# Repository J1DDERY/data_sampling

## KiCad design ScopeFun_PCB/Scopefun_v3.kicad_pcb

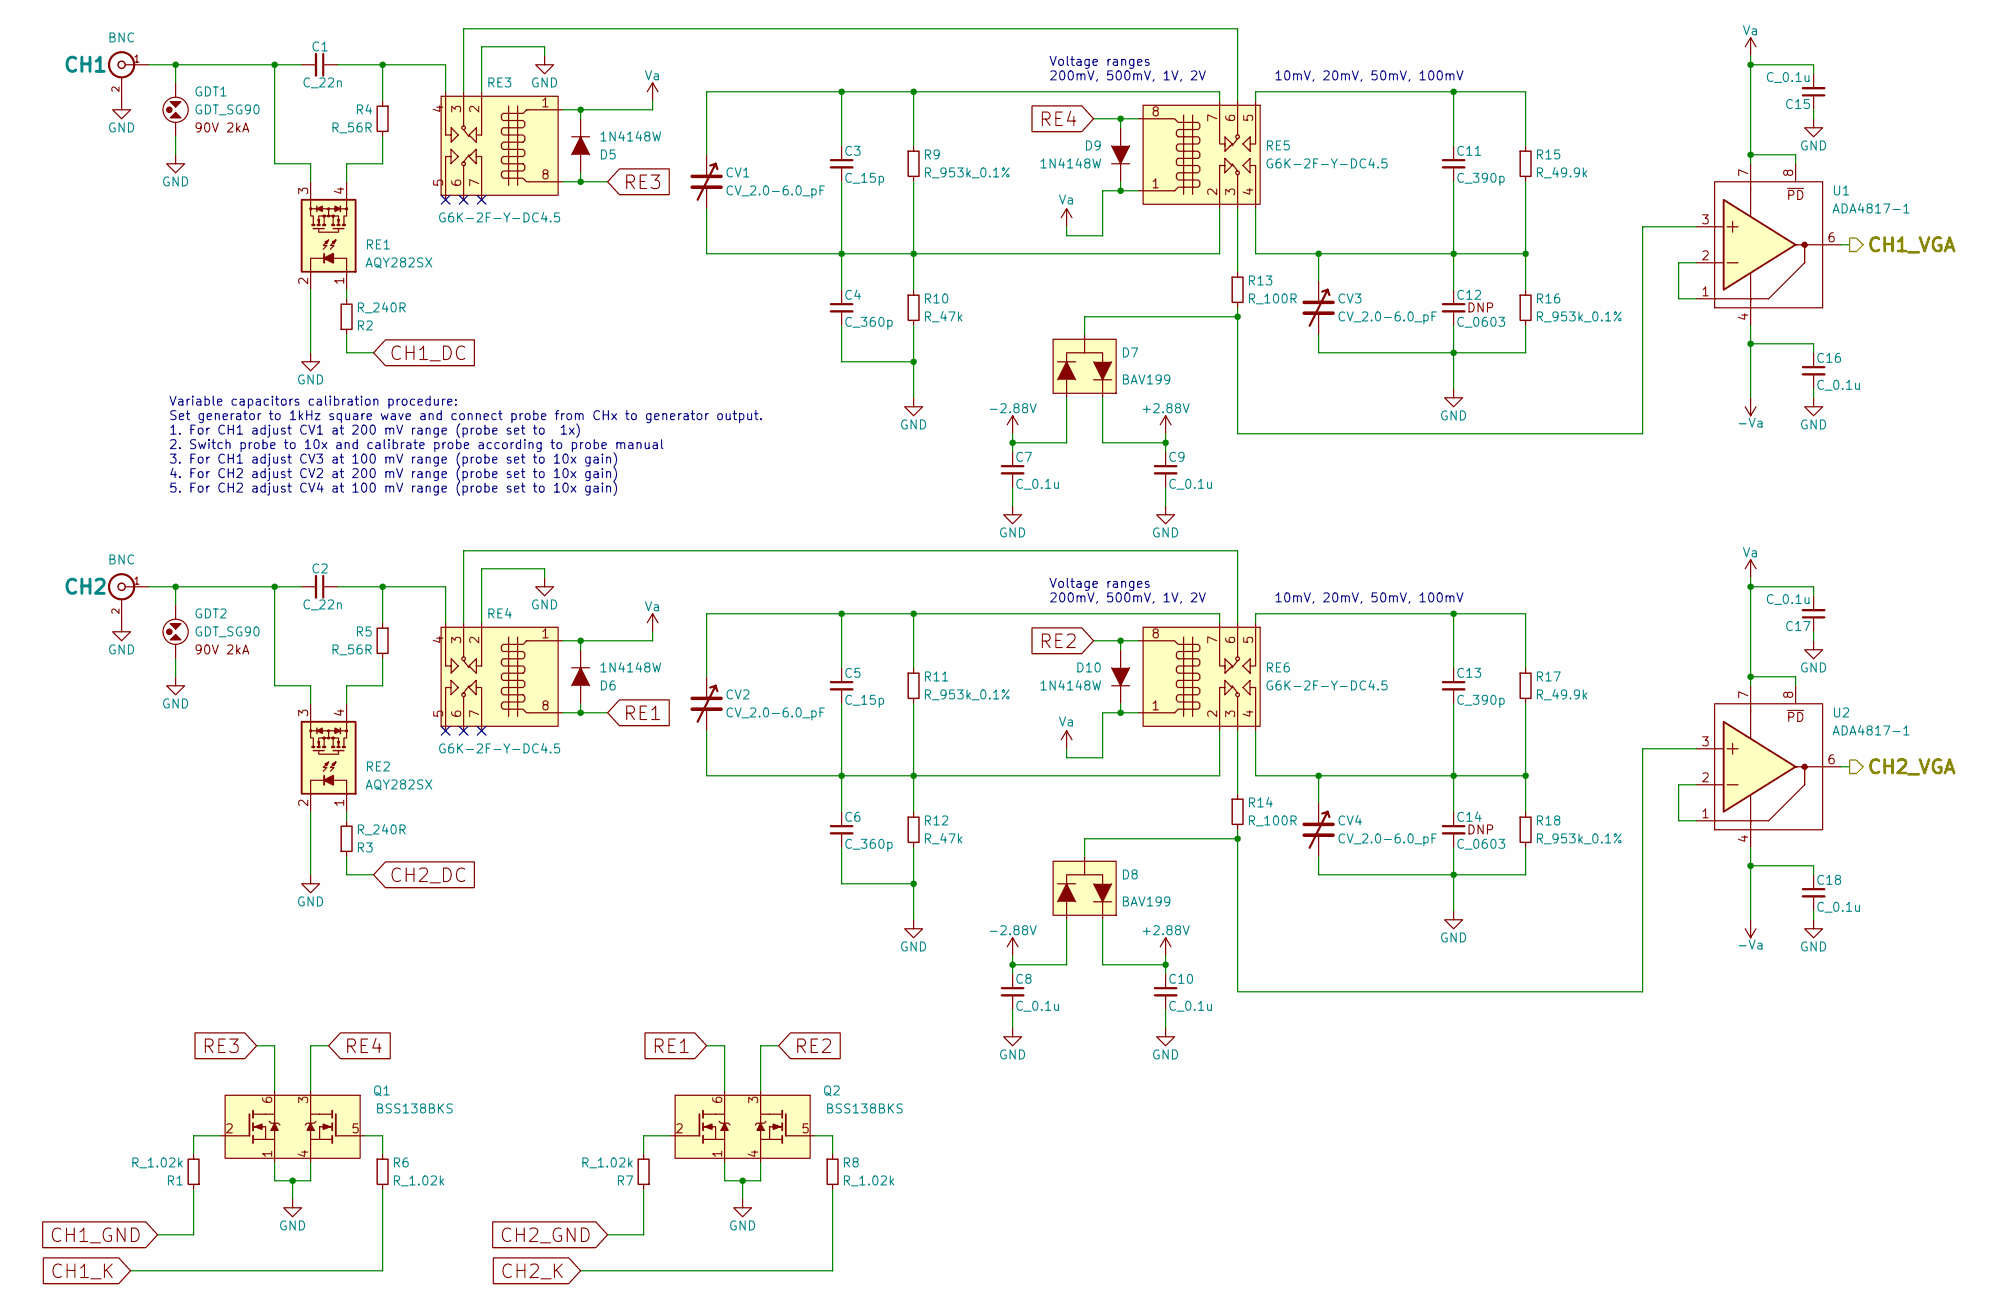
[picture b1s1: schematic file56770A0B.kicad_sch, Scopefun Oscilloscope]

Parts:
C1, C2: C_22n; C_0603; MFG Part# C0603C223K1RACTU
C3, C5: C_15p; C_0603; MFG Part# 885012006074
C4, C6: C_360p; C_0603; MFG Part# C0603C361G5GACTU
C7, C8, C9, C10, C15, C16, C17, C18: C_0.1u; C_0603; MFG Part# C0603C104K4RACTU
C11, C13: C_390p; C_0603; MFG Part# VJ0603A391GXAPW1BC
C12, C14: C_0603
CH1, CH2: BNC; BNC-5-1634556-0; MFG Part# 5-1634556-0
CV1, CV2, CV3, CV4: CV_2.0-6.0_pF; SGC3; MFG Part# SGC3S060
D5, D6, D9, D10: 1N4148W; SOD123; MFG Part# 1N4148W-7-F
D7, D8: BAV199; SOT23; MFG Part# BAV199-7-F
GDT1, GDT2: GDT_SG90; GDT_SG; MFG Part# SG90
Q1, Q2: BSS138BKS; SOT363; MFG Part# BSS138PS,115
R1, R6, R7, R8: R_1.02k; R_0603; MFG Part# ERJ-3EKF1021V
R2, R3: R_240R; R_0603; MFG Part# ERJ-3EKF2400V
R4, R5: R_56R; R_0603; MFG Part# ERJ-3EKF56R0V
R9, R11, R16, R18: R_953k_0.1%; R_0805; MFG Part# ERA-6AEB9533V
R10, R12: R_47k; R_0603; MFG Part# ERJ-3EKF4702V
R13, R14: R_100R; R_0603; MFG Part# ERJ-3EKF1000V
R15, R17: R_49.9k; R_0603; MFG Part# ERJ-3EKF4992V
RE1, RE2: AQY282SX; SOP-4; MFG Part# AQY282SX
RE3, RE4, RE5, RE6: G6K-2F-Y-DC4.5; G6K-2F-Y; MFG Part# G6K-2F-Y-DC4.5
U1, U2: ADA4817-1; SOIC8; MFG Part# ADA4817-1ARDZ

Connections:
+2.88V: C9.1, C10.1, D7.2, D8.2; also elsewhere on the board
-2.88V: C7.1, C8.1, D7.1, D8.1; also elsewhere on the board
-Va: C16.1, C18.1, U1.4 (-Vs), U2.4 (-Vs); also elsewhere on the board
/ANALOG INPUTS/CH1_VGA: U1.6 (OUT); also elsewhere on the board
/ANALOG INPUTS/CH2_VGA: U2.6 (OUT); also elsewhere on the board
CH1_DC: R2.1; also elsewhere on the board
CH1_GND: R1.1; also elsewhere on the board
CH1_K: R6.2; also elsewhere on the board
CH2_DC: R3.1; also elsewhere on the board
CH2_GND: R7.1; also elsewhere on the board
CH2_K: R8.2; also elsewhere on the board
GND: C4.2, C6.2, C7.2, C8.2, C9.2, C10.2, C12.2, C14.2, C15.1, C16.2, C17.1, C18.2, CH1.2 (Ext), CH2.2 (Ext), CV3.2, CV4.2, GDT1.2, GDT2.2, Q1.1 (S1), Q1.4 (S2), Q2.1 (S1), Q2.4 (S2), R10.2, R12.2, R16.2, R18.2, RE1.2, RE2.2, RE3.2, RE4.2; also elsewhere on the board
unnamed: C1.1, R4.1, RE3.4
unnamed: C2.1, R5.1, RE4.4
unnamed: C3.1, CV1.1, R9.1, RE5.7
unnamed: C3.2, C4.1, CV1.2, R9.2, R10.1, RE5.2
unnamed: C5.1, CV2.1, R11.1, RE6.7
unnamed: C5.2, C6.1, CV2.2, R11.2, R12.1, RE6.2
unnamed: C11.1, R15.1, RE5.5
unnamed: C11.2, C12.1, CV3.1, R15.2, R16.1, RE5.4
unnamed: C13.1, R17.1, RE6.5
unnamed: C13.2, C14.1, CV4.1, R17.2, R18.1, RE6.4
unnamed: C1.2, CH1.1 (In), GDT1.1, RE1.3
unnamed: C2.2, CH2.1 (In), GDT2.1, RE2.3
unnamed: Q1.2 (G1), R1.2
unnamed: Q1.5 (G2), R6.1
unnamed: Q2.2 (G1), R7.2
unnamed: Q2.5 (G2), R8.1
unnamed: R2.2, RE1.1
unnamed: R3.2, RE2.1
unnamed: R4.2, RE1.4
unnamed: R5.2, RE2.4
unnamed: R13.1, RE5.3
unnamed: R14.1, RE6.3
unnamed: RE3.3, RE5.6
unnamed: RE4.3, RE6.6
unnamed: D7.3, R13.2, U1.3 (+IN)
unnamed: U1.1 (FB), U1.2 (-IN)
unnamed: D8.3, R14.2, U2.3 (+IN)
unnamed: U2.1 (FB), U2.2 (-IN)
RE1: D6.2 (A), Q2.6 (D1), RE4.8
RE2: D10.2 (A), Q2.3 (D2), RE6.8
RE3: D5.2 (A), Q1.6 (D1), RE3.8
RE4: D9.2 (A), Q1.3 (D2), RE5.8
Va: C15.2, C17.2, D5.1 (K), D6.1 (K), D9.1 (K), D10.1 (K), RE3.1, RE4.1, RE5.1, RE6.1, U1.7 (+Vs), U1.8 (~PD), U2.7 (+Vs), U2.8 (~PD); also elsewhere on the board

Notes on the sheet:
10mV, 20mV, 50mV, 100mV
Voltage ranges 200mV, 500mV, 1V, 2V
Variable capacitors calibration procedure: Set generator to 1kHz square wave and connect probe from CHx to generator output. 1. For CH1 adjust CV1 at 200 mV range (probe set to 1x) 2. Switch probe to 10x and calibrate probe according to probe manual 3. For CH1 adjust CV3 at 100 mV range (probe set 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

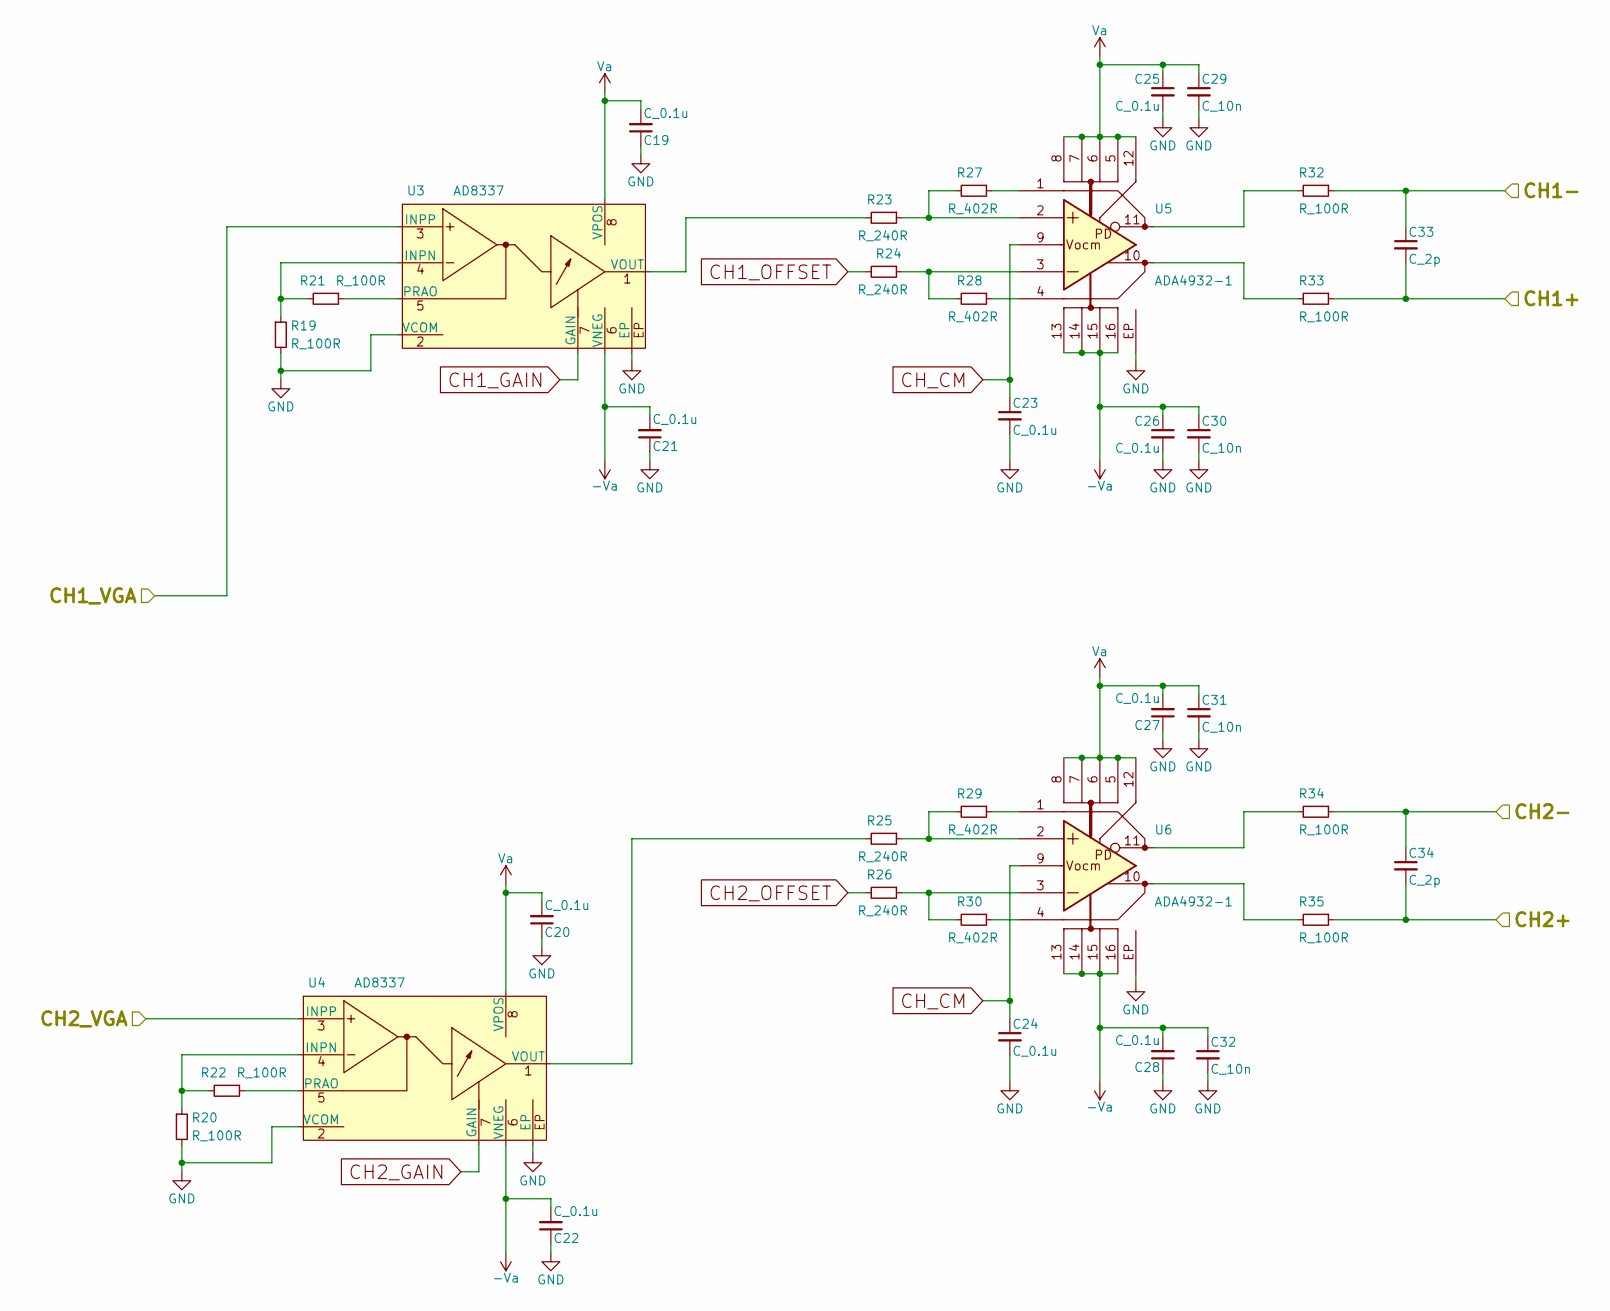
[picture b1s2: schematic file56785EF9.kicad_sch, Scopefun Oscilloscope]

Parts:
C19, C20, C21, C22, C23, C24, C25, C26, C27, C28: C_0.1u; C_0603; MFG Part# C0603C104K4RACTU
C29, C30, C31, C32: C_10n; C_0402; MFG Part# 885012205012
C33, C34: C_2p; C_0603; MFG Part# C1608C0G2A020C080AA
R19, R20, R21, R22, R32, R33, R34, R35: R_100R; R_0603; MFG Part# ERJ-3EKF1000V
R23, R24, R25, R26: R_240R; R_0603; MFG Part# ERJ-3EKF2400V
R27, R28, R29, R30: R_402R; R_0603; MFG Part# ERJ-3EKF4020V
U3, U4: AD8337; CP-8-2; MFG Part# AD8337BCPZ-REEL7
U5, U6: ADA4932-1; CP-16-2; MFG Part# ADA4932-1YCPZ-R7

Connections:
-Va: C21.2, C22.2, C26.1, C28.2, C30.1, C32.1, U3.6 (VNEG), U4.6 (VNEG), U5.13 (-Vs), U5.14 (-Vs), U5.15 (-Vs), U5.16 (-Vs), U6.13 (-Vs), U6.14 (-Vs), U6.15 (-Vs), U6.16 (-Vs); also elsewhere on the board
/ADC/CH1+: C33.2, R33.1; also elsewhere on the board
/ADC/CH1-: C33.1, R32.1; also elsewhere on the board
/ADC/CH2+: C34.2, R35.1; also elsewhere on the board
/ADC/CH2-: C34.1, R34.1; also elsewhere on the board
/ANALOG INPUTS/CH1_VGA: U3.3 (INPP); also elsewhere on the board
/ANALOG INPUTS/CH2_VGA: U4.3 (INPP); also elsewhere on the board
CH1_GAIN: U3.7 (GAIN); also elsewhere on the board
CH1_OFFSET: R24.2; also elsewhere on the board
CH2_GAIN: U4.7 (GAIN); also elsewhere on the board
CH2_OFFSET: R26.2; also elsewhere on the board
CH_CM: C23.1, C24.1, U5.9 (Vocm), U6.9 (Vocm); also elsewhere on the board
GND: C19.1, C20.1, C21.1, C22.1, C23.2, C24.2, C25.2, C26.2, C27.1, C28.1, C29.2, C30.2, C31.2, C32.2, R19.2, R20.2, U3.2 (VCOM), U3.EP, U4.2 (VCOM), U4.EP, U5.EP, U6.EP; also elsewhere on the board
unnamed: R19.1, R21.2, U3.4 (INPN)
unnamed: R21.1, U3.5 (PRAO)
unnamed: R23.2, U3.1 (VOUT)
unnamed: R20.1, R22.2, U4.4 (INPN)
unnamed: R22.1, U4.5 (PRAO)
unnamed: R25.2, U4.1 (VOUT)
unnamed: R28.1, U5.4 (+FB)
unnamed: R23.1, R27.2, U5.2 (+IN)
unnamed: R33.2, U5.10 (+OUT)
unnamed: R27.1, U5.1 (-FB)
unnamed: R24.1, R28.2, U5.3 (-IN)
unnamed: R32.2, U5.11 (-OUT)
unnamed: R30.1, U6.4 (+FB)
unnamed: R25.1, R29.2, U6.2 (+IN)
unnamed: R35.2, U6.10 (+OUT)
unnamed: R29.1, U6.1 (-FB)
unnamed: R26.1, R30.2, U6.3 (-IN)
unnamed: R34.2, U6.11 (-OUT)
Va: C19.2, C20.2, C25.1, C27.2, C29.1, C31.1, U3.8 (VPOS), U4.8 (VPOS), U5.5 (+Vs), U5.6 (+Vs), U5.7 (+Vs), U5.8 (+Vs), U5.12 (r~PD), U6.5 (+Vs), U6.6 (+Vs), U6.7 (+Vs), U6.8 (+Vs), U6.12 (r~PD); also elsewhere on the board

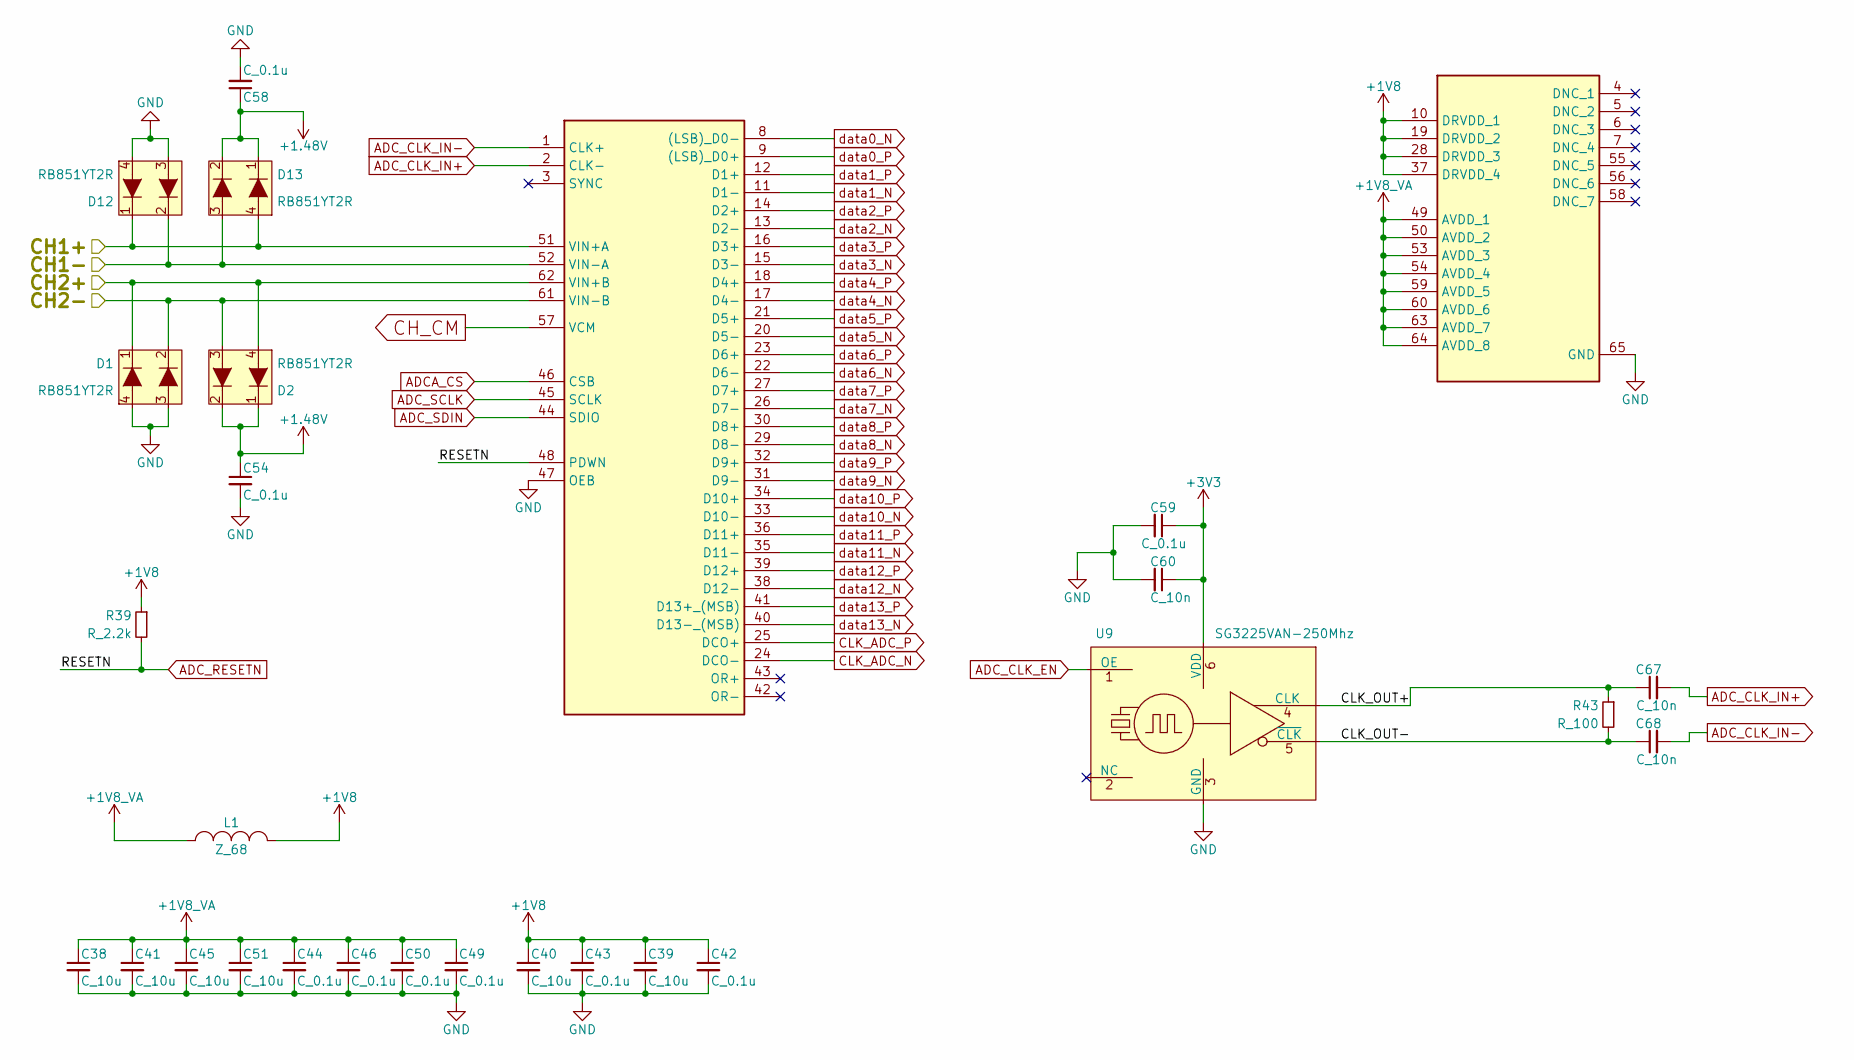
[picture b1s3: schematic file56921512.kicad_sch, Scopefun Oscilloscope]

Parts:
C38, C39, C40, C41, C45, C51: C_10u; C_0603; MFG Part# C0603C104K4RACTU
C42, C43, C44, C46, C49, C50, C54, C58, C59: C_0.1u; C_0603; MFG Part# C0603C104K4RACTU
C60, C67, C68: C_10n; C_0402; MFG Part# 885012205012
D1, D2, D12, D13: RB851YT2R; SOT-543; MFG Part# RB851YT2R
IC1: AD9643BCPZ-250; QFN50P900X900X100-65N-D; Manufacturer_Part_Number AD9643BCPZ-250; Mouser Part Number 584-AD9643BCPZ-250
L1: Z_68; L_0805; MFG Part# 782853680
R39: R_2.2k; R_0603; MFG Part# ERJ-3EKF2201V
R43: R_100; R_0402; MFG Part# ERJ-2RKF1000X
U9: SG3225VAN-250Mhz; 3.2X2.5_SMD_6_EPSON; MFG Part# SG3225VAN 250.000000M-KEGA3

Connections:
+1.48V: C54.1, C58.1, D2.1, D2.2, D13.1, D13.2; also elsewhere on the board
+1V8: C39.1, C40.1, C42.1, C43.1, IC1.10 (DRVDD_1), IC1.19 (DRVDD_2), IC1.28 (DRVDD_3), IC1.37 (DRVDD_4), L1.1, R39.1; also elsewhere on the board
+1V8_VA: C38.1, C41.1, C44.1, C45.1, C46.1, C49.1, C50.1, C51.1, IC1.49 (AVDD_1), IC1.50 (AVDD_2), IC1.53 (AVDD_3), IC1.54 (AVDD_4), IC1.59 (AVDD_5), IC1.60 (AVDD_6), IC1.63 (AVDD_7), IC1.64 (AVDD_8), L1.2
+3V3: C59.1, C60.1, U9.6 (VDD); also elsewhere on the board
/ADC/CH1+: D12.1, D13.4, IC1.51 (VIN+A); also elsewhere on the board
/ADC/CH1-: D12.2, D13.3, IC1.52 (VIN-A); also elsewhere on the board
/ADC/CH2+: D1.1, D2.4, IC1.62 (VIN+B); also elsewhere on the board
/ADC/CH2-: D1.2, D2.3, IC1.61 (VIN-B); also elsewhere on the board
/ADC/CLK_OUT+: C67.1, R43.1, U9.4 (CLK)
/ADC/CLK_OUT-: C68.1, R43.2, U9.5 (~CLK)
ADCA_CS: IC1.46 (CSB); also elsewhere on the board
ADC_CLK_EN: U9.1 (OE); also elsewhere on the board
ADC_CLK_IN+: C67.2, IC1.2 (CLK-)
ADC_CLK_IN-: C68.2, IC1.1 (CLK+)
ADC_RESETN: IC1.48 (PDWN), R39.2; also elsewhere on the board
ADC_SCLK: IC1.45 (SCLK); also elsewhere on the board
ADC_SDIN: IC1.44 (SDIO); also elsewhere on the board
CH_CM: IC1.57 (VCM); also elsewhere on the board
CLK_ADC_N: IC1.24 (DCO-); also elsewhere on the board
CLK_ADC_P: IC1.25 (DCO+); also elsewhere on the board
GND: C38.2, C39.2, C40.2, C41.2, C42.2, C43.2, C44.2, C45.2, C46.2, C49.2, C50.2, C51.2, C54.2, C58.2, C59.2, C60.2, D1.3, D1.4, D12.3, D12.4, IC1.47 (OEB), IC1.65 (GND), U9.3 (GND); also elsewhere on the board
data0_N: IC1.8 ((LSB)_D0-); also elsewhere on the board
data0_P: IC1.9 ((LSB)_D0+); also elsewhere on the board
data1_N: IC1.11 (D1-); also elsewhere on the board
data1_P: IC1.12 (D1+); also elsewhere on the board
data2_N: IC1.13 (D2-); also elsewhere on the board
data2_P: IC1.14 (D2+); also elsewhere on the board
data3_N: IC1.15 (D3-); also elsewhere on the board
data3_P: IC1.16 (D3+); also elsewhere on the board
data4_N: IC1.17 (D4-); also elsewhere on the board
data4_P: IC1.18 (D4+); also elsewhere on the board
data5_N: IC1.20 (D5-); also elsewhere on the board
data5_P: IC1.21 (D5+); also elsewhere on the board
data6_N: IC1.22 (D6-); also elsewhere on the board
data6_P: IC1.23 (D6+); also elsewhere on the board
data7_N: IC1.26 (D7-); also elsewhere on the board
data7_P: IC1.27 (D7+); also elsewhere on the board
data8_N: IC1.29 (D8-); also elsewhere on the board
data8_P: IC1.30 (D8+); also elsewhere on the board
data9_N: IC1.31 (D9-); also elsewhere on the board
data9_P: IC1.32 (D9+); also elsewhere on the board
data10_N: IC1.33 (D10-); also elsewhere on the board
data10_P: IC1.34 (D10+); also elsewhere on the board
data11_N: IC1.35 (D11-); also elsewhere on the board
data11_P: IC1.36 (D11+); also elsewhere on the board
data12_N: IC1.38 (D12-); also elsewhere on the board
data12_P: IC1.39 (D12+); also elsewhere on the board
data13_N: IC1.40 (D13-_(MSB)); also elsewhere on the board
data13_P: IC1.41 (D13+_(MSB)); also elsewhere on the board

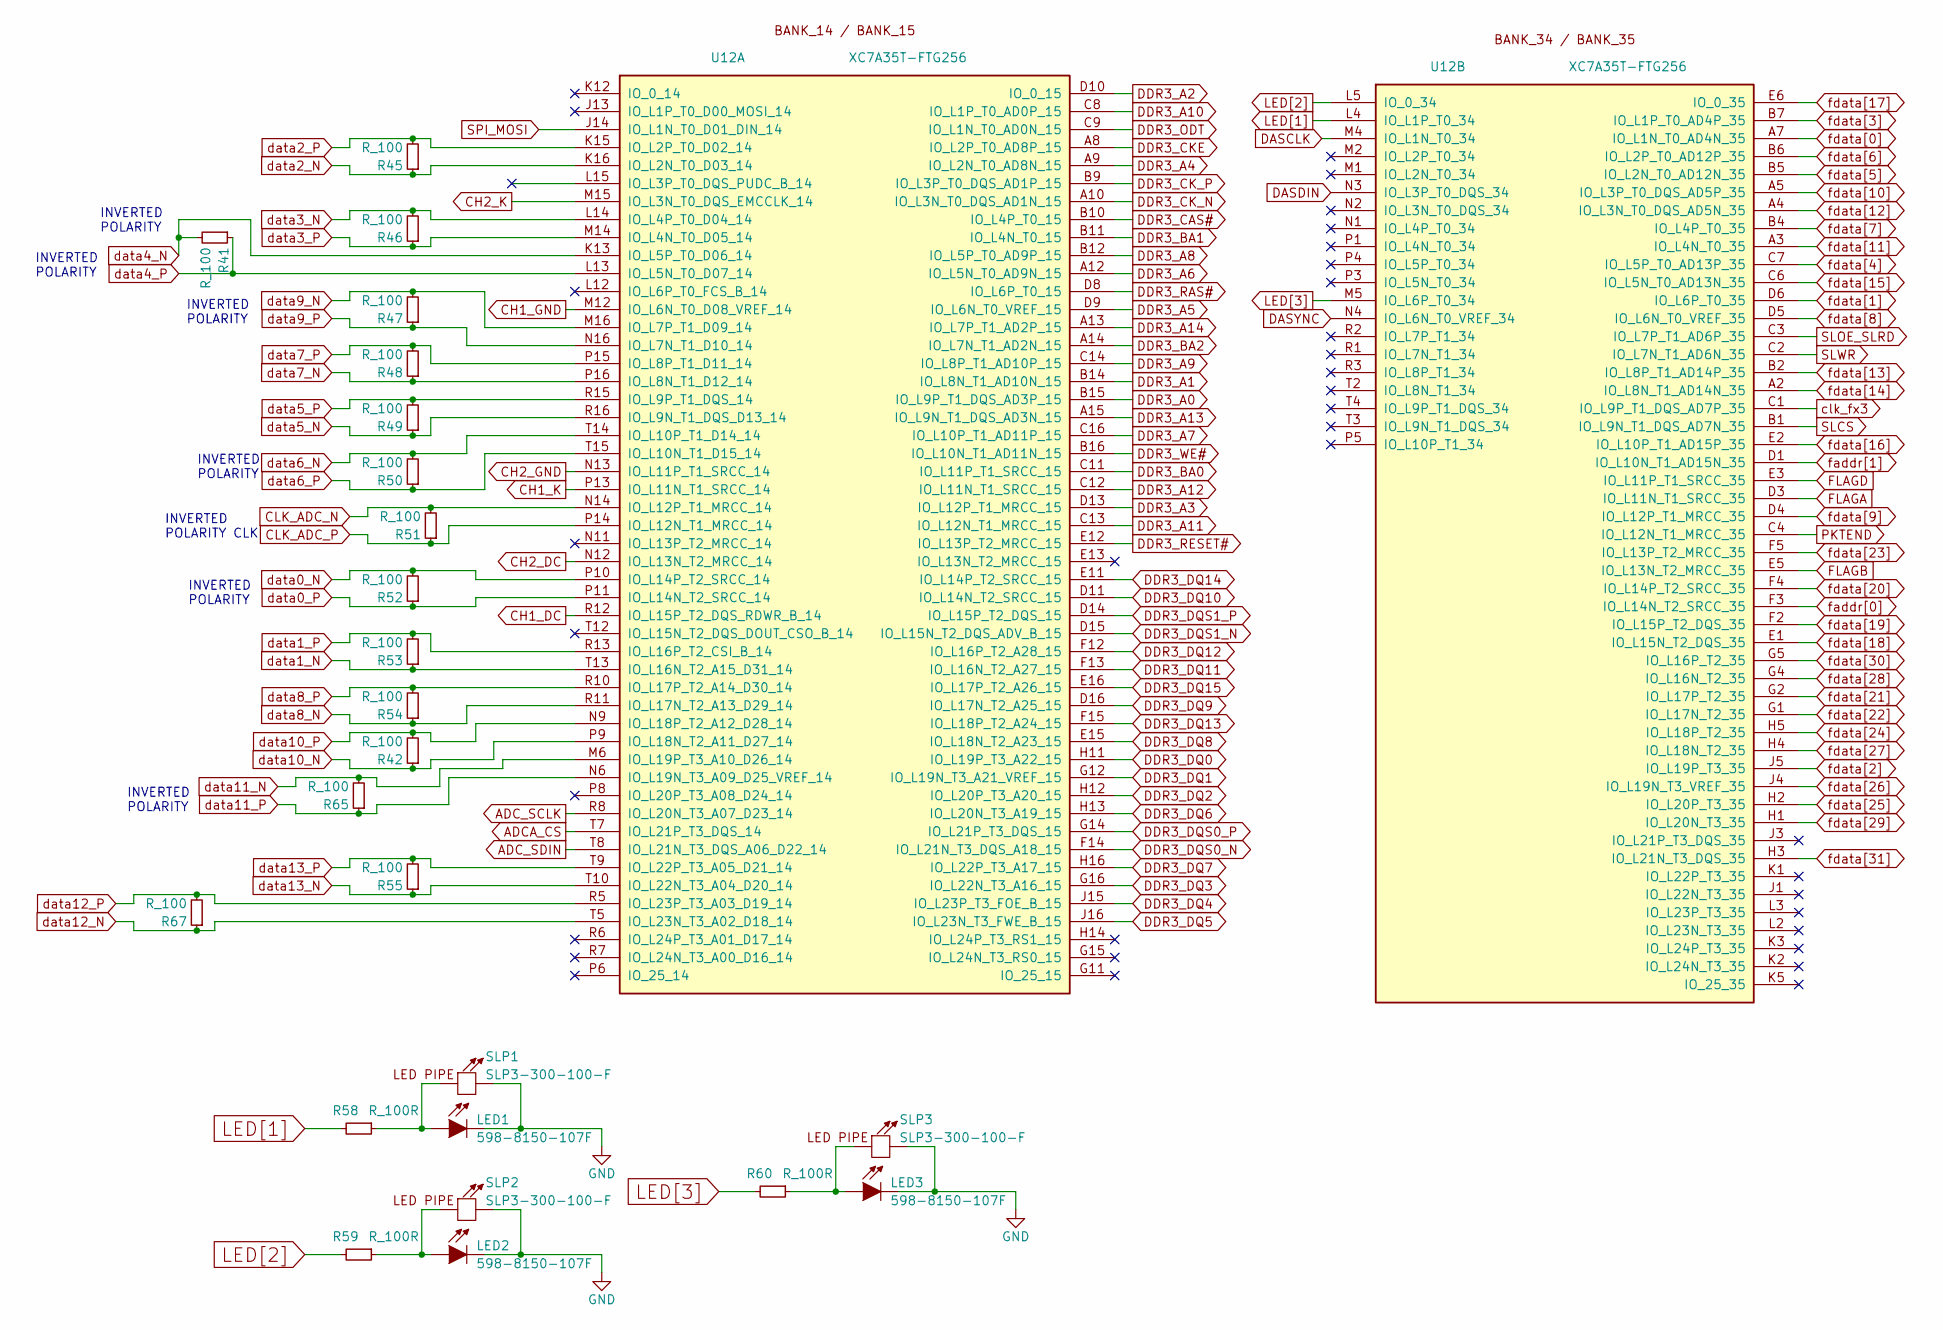
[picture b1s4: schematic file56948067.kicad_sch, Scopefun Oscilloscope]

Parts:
LED1, LED2, LED3: 598-8150-107F; LED_0805; MFG Part# 598-8150-107F
R41, R42, R45, R46, R47, R48, R49, R50, R51, R52, R53, R54, R55, R65, R67: R_100; R_0402; MFG Part# ERJ-2RKF1000X
R58, R59, R60: R_100R; R_0603; MFG Part# ERJ-3EKF1000V
SLP1, SLP2, SLP3: SLP3-300-100-F; SLP3-300-100-R; MFG Part# SLP3-300-100-F
U12: XC7A35T-FTG256; BGA256_FTG256; MFG Part# XC7A35T-2FTG256I

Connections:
ADCA_CS: U12.T7 (IO_L21P_T3_DQS_14); also elsewhere on the board
ADC_SCLK: U12.R8 (IO_L20N_T3_A07_D23_14); also elsewhere on the board
ADC_SDIN: U12.T8 (IO_L21N_T3_DQS_A06_D22_14); also elsewhere on the board
CH1_DC: U12.R12 (IO_L15P_T2_DQS_RDWR_B_14); also elsewhere on the board
CH1_GND: U12.M12 (IO_L6N_T0_D08_VREF_14); also elsewhere on the board
CH1_K: U12.P13 (IO_L11N_T1_SRCC_14); also elsewhere on the board
CH2_DC: U12.N12 (IO_L13N_T2_MRCC_14); also elsewhere on the board
CH2_GND: U12.N13 (IO_L11P_T1_SRCC_14); also elsewhere on the board
CH2_K: U12.M15 (IO_L3N_T0_DQS_EMCCLK_14); also elsewhere on the board
CLK_ADC_N: R51.2, U12.N14 (IO_L12P_T1_MRCC_14); also elsewhere on the board
CLK_ADC_P: R51.1, U12.P14 (IO_L12N_T1_MRCC_14); also elsewhere on the board
DASCLK: U12.M4 (IO_L1N_T0_34); also elsewhere on the board
DASDIN: U12.N3 (IO_L3P_T0_DQS_34); also elsewhere on the board
DASYNC: U12.N4 (IO_L6N_T0_VREF_34); also elsewhere on the board
DDR3_A0: U12.B15 (IO_L9P_T1_DQS_AD3P_15); also elsewhere on the board
DDR3_A1: U12.B14 (IO_L8N_T1_AD10N_15); also elsewhere on the board
DDR3_A2: U12.D10 (IO_0_15); also elsewhere on the board
DDR3_A3: U12.D13 (IO_L12P_T1_MRCC_15); also elsewhere on the board
DDR3_A4: U12.A9 (IO_L2N_T0_AD8N_15); also elsewhere on the board
DDR3_A5: U12.D9 (IO_L6N_T0_VREF_15); also elsewhere on the board
DDR3_A6: U12.A12 (IO_L5N_T0_AD9N_15); also elsewhere on the board
DDR3_A7: U12.C16 (IO_L10P_T1_AD11P_15); also elsewhere on the board
DDR3_A8: U12.B12 (IO_L5P_T0_AD9P_15); also elsewhere on the board
DDR3_A9: U12.C14 (IO_L8P_T1_AD10P_15); also elsewhere on the board
DDR3_A10: U12.C8 (IO_L1P_T0_AD0P_15); also elsewhere on the board
DDR3_A11: U12.C13 (IO_L12N_T1_MRCC_15); also elsewhere on the board
DDR3_A12: U12.C12 (IO_L11N_T1_SRCC_15); also elsewhere on the board
DDR3_A13: U12.A15 (IO_L9N_T1_DQS_AD3N_15); also elsewhere on the board
DDR3_A14: U12.A13 (IO_L7P_T1_AD2P_15); also elsewhere on the board
DDR3_BA0: U12.C11 (IO_L11P_T1_SRCC_15); also elsewhere on the board
DDR3_BA1: U12.B11 (IO_L4N_T0_15); also elsewhere on the board
DDR3_BA2: U12.A14 (IO_L7N_T1_AD2N_15); also elsewhere on the board
DDR3_CAS#: U12.B10 (IO_L4P_T0_15); also elsewhere on the board
DDR3_CKE: U12.A8 (IO_L2P_T0_AD8P_15); also elsewhere on the board
DDR3_CK_N: U12.A10 (IO_L3N_T0_DQS_AD1N_15); also elsewhere on the board
DDR3_CK_P: U12.B9 (IO_L3P_T0_DQS_AD1P_15); also elsewhere on the board
DDR3_DQ0: U12.H11 (IO_L19P_T3_A22_15); also elsewhere on the board
DDR3_DQ1: U12.G12 (IO_L19N_T3_A21_VREF_15); also elsewhere on the board
DDR3_DQ2: U12.H12 (IO_L20P_T3_A20_15); also elsewhere on the board
DDR3_DQ3: U12.G16 (IO_L22N_T3_A16_15); also elsewhere on the board
DDR3_DQ4: U12.J15 (IO_L23P_T3_FOE_B_15); also elsewhere on the board
DDR3_DQ5: U12.J16 (IO_L23N_T3_FWE_B_15); also elsewhere on the board
DDR3_DQ6: U12.H13 (IO_L20N_T3_A19_15); also elsewhere on the board
DDR3_DQ7: U12.H16 (IO_L22P_T3_A17_15); also elsewhere on the board
DDR3_DQ8: U12.E15 (IO_L18N_T2_A23_15); also elsewhere on the board
DDR3_DQ9: U12.D16 (IO_L17N_T2_A25_15); also elsewhere on the board
DDR3_DQ10: U12.D11 (IO_L14N_T2_SRCC_15); also elsewhere on the board
DDR3_DQ11: U12.F13 (IO_L16N_T2_A27_15); also elsewhere on the board
DDR3_DQ12: U12.F12 (IO_L16P_T2_A28_15); also elsewhere on the board
DDR3_DQ13: U12.F15 (IO_L18P_T2_A24_15); also elsewhere on the board
DDR3_DQ14: U12.E11 (IO_L14P_T2_SRCC_15); also elsewhere on the board
DDR3_DQ15: U12.E16 (IO_L17P_T2_A26_15); also elsewhere on the board
DDR3_DQS0_N: U12.F14 (IO_L21N_T3_DQS_A18_15); also elsewhere on the board
DDR3_DQS0_P: U12.G14 (IO_L21P_T3_DQS_15); also elsewhere on the board
DDR3_DQS1_N: U12.D15 (IO_L15N_T2_DQS_ADV_B_15); also elsewhere on the board
DDR3_DQS1_P: U12.D14 (IO_L15P_T2_DQS_15); also elsewhere on the board
DDR3_ODT: U12.C9 (IO_L1N_T0_AD0N_15); also elsewhere on the board
DDR3_RAS#: U12.D8 (IO_L6P_T0_15); also elsewhere on the board
DDR3_RESET#: U12.E12 (IO_L13P_T2_MRCC_15); also elsewhere on the board
DDR3_WE#: U12.B16 (IO_L10N_T1_AD11N_15); also elsewhere on the board
FLAGA: U12.D3 (IO_L11N_T1_SRCC_35); also elsewhere on the board
FLAGB: U12.E5 (IO_L13N_T2_MRCC_35); also elsewhere on the board
FLAGD: U12.E3 (IO_L11P_T1_SRCC_35); also elsewhere on the board
GND: LED1.1 (K), LED2.1 (K), LED3.1 (K), SLP1.1 (K), SLP2.1 (K), SLP3.1 (K); also elsewhere on the board
LED[1]: R58.2, U12.L4 (IO_L1P_T0_34)
LED[2]: R59.2, U12.L5 (IO_0_34)
LED[3]: R60.2, U12.M5 (IO_L6P_T0_34)
unnamed: LED1.2 (A), R58.1, SLP1.2 (A)
unnamed: LED2.2 (A), R59.1, SLP2.2 (A)
unnamed: LED3.2 (A), R60.1, SLP3.2 (A)
PKTEND: U12.C4 (IO_L12N_T1_MRCC_35); also elsewhere on the board
RE7: U12.L12 (IO_L6P_T0_FCS_B_14)
SLCS: U12.B1 (IO_L9N_T1_DQS_AD7N_35); also elsewhere on the board
SLOE_SLRD: U12.C3 (IO_L7P_T1_AD6P_35); also elsewhere on the board
SLWR: U12.C2 (IO_L7N_T1_AD6N_35); also elsewhere on the board
SPI_MOSI: U12.J14 (IO_L1N_T0_D01_DIN_14); also elsewhere on the board
clk_fx3: U12.C1 (IO_L9P_T1_DQS_AD7P_35); also elsewhere on the board
data0_N: R52.2, U12.P10 (IO_L14P_T2_SRCC_14); also elsewhere on the board
data0_P: R52.1, U12.P11 (IO_L14N_T2_SRCC_14); also elsewhere on the board
data1_N: R53.1, U12.T13 (IO_L16N_T2_A15_D31_14); also elsewhere on the board
data1_P: R53.2, U12.R13 (IO_L16P_T2_CSI_B_14); also elsewhere on the board
data2_N: R45.1, U12.K16 (IO_L2N_T0_D03_14); also elsewhere on the board
data2_P: R45.2, U12.K15 (IO_L2P_T0_D02_14); also elsewhere on the board
data3_N: R46.2, U12.L14 (IO_L4P_T0_D04_14); also elsewhere on the board
data3_P: R46.1, U12.M14 (IO_L4N_T0_D05_14); also elsewhere on the board
data4_N: R41.2, U12.K13 (IO_L5P_T0_D06_14); also elsewhere on the board
data4_P: R41.1, U12.L13 (IO_L5N_T0_D07_14); also elsewhere on the board
data5_N: R49.1, U12.R16 (IO_L9N_T1_DQS_D13_14); also elsewhere on the board
data5_P: R49.2, U12.R15 (IO_L9P_T1_DQS_14); also elsewhere on the board
data6_N: R50.2, U12.T14 (IO_L10P_T1_D14_14); also elsewhere on the board
data6_P: R50.1, U12.T15 (IO_L10N_T1_D15_14); also elsewhere on the board
data7_N: R48.1, U12.P16 (IO_L8N_T1_D12_14); also elsewhere on the board
data7_P: R48.2, U12.P15 (IO_L8P_T1_D11_14); also elsewhere on the board
data8_N: R54.1, U12.R11 (IO_L17N_T2_A13_D29_14); also elsewhere on the board
data8_P: R54.2, U12.R10 (IO_L17P_T2_A14_D30_14); also elsewhere on the board
data9_N: R47.2, U12.M16 (IO_L7P_T1_D09_14); also elsewhere on the board
data9_P: R47.1, U12.N16 (IO_L7N_T1_D10_14); also elsewhere on the board
data10_N: R42.1, U12.P9 (IO_L18N_T2_A11_D27_14); also elsewhere on the board
data10_P: R42.2, U12.N9 (IO_L18P_T2_A12_D28_14); also elsewhere on the board
data11_N: R65.2, U12.M6 (IO_L19P_T3_A10_D26_14); also elsewhere on the board
data11_P: R65.1, U12.N6 (IO_L19N_T3_A09_D25_VREF_14); also elsewhere on the board
data12_N: R67.1, U12.T5 (IO_L23N_T3_A02_D18_14); also elsewhere on the board
data12_P: R67.2, U12.R5 (IO_L23P_T3_A03_D19_14); also elsewhere on the board
data13_N: R55.1, U12.T10 (IO_L22N_T3_A04_D20_14); also elsewhere on the board
data13_P: R55.2, U12.T9 (IO_L22P_T3_A05_D21_14); also elsewhere on the board
faddr[0]: U12.F3 (IO_L14N_T2_SRCC_35); also elsewhere on the board
faddr[1]: U12.D1 (IO_L10N_T1_AD15N_35); also elsewhere on the board
fdata[0]: U12.A7 (IO_L1N_T0_AD4N_35); also elsewhere on the board
fdata[1]: U12.D6 (IO_L6P_T0_35); also elsewhere on the board
fdata[2]: U12.J5 (IO_L19P_T3_35); also elsewhere on the board
fdata[3]: U12.B7 (IO_L1P_T0_AD4P_35); also elsewhere on the board
fdata[4]: U12.C7 (IO_L5P_T0_AD13P_35); also elsewhere on the board
fdata[5]: U12.B5 (IO_L2N_T0_AD12N_35); also elsewhere on the board
fdata[6]: U12.B6 (IO_L2P_T0_AD12P_35); also elsewhere on the board
fdata[7]: U12.B4 (IO_L4P_T0_35); also elsewhere on the board
fdata[8]: U12.D5 (IO_L6N_T0_VREF_35); also elsewhere on the board
fdata[9]: U12.D4 (IO_L12P_T1_MRCC_35); also elsewhere on the board
fdata[10]: U12.A5 (IO_L3P_T0_DQS_AD5P_35); also elsewhere on the board
fdata[11]: U12.A3 (IO_L4N_T0_35); also elsewhere on the board
fdata[12]: U12.A4 (IO_L3N_T0_DQS_AD5N_35); also elsewhere on the board
fdata[13]: U12.B2 (IO_L8P_T1_AD14P_35); also elsewhere on the board
fdata[14]: U12.A2 (IO_L8N_T1_AD14N_35); also elsewhere on the board
fdata[15]: U12.C6 (IO_L5N_T0_AD13N_35); also elsewhere on the board
fdata[16]: U12.E2 (IO_L10P_T1_AD15P_35); also elsewhere on the board
fdata[17]: U12.E6 (IO_0_35); also elsewhere on the board
fdata[18]: U12.E1 (IO_L15N_T2_DQS_35); also elsewhere on the board
fdata[19]: U12.F2 (IO_L15P_T2_DQS_35); also elsewhere on the board
fdata[20]: U12.F4 (IO_L14P_T2_SRCC_35); also elsewhere on the board
fdata[21]: U12.G2 (IO_L17P_T2_35); also elsewhere on the board
fdata[22]: U12.G1 (IO_L17N_T2_35); also elsewhere on the board
fdata[23]: U12.F5 (IO_L13P_T2_MRCC_35); also elsewhere on the board
fdata[24]: U12.H5 (IO_L18P_T2_35); also elsewhere on the board
fdata[25]: U12.H2 (IO_L20P_T3_35); also elsewhere on the board
fdata[26]: U12.J4 (IO_L19N_T3_VREF_35); also elsewhere on the board
fdata[27]: U12.H4 (IO_L18N_T2_35); also elsewhere on the board
fdata[28]: U12.G4 (IO_L16N_T2_35); also elsewhere on the board
fdata[29]: U12.H1 (IO_L20N_T3_35); also elsewhere on the board
fdata[30]: U12.G5 (IO_L16P_T2_35); also elsewhere on the board
fdata[31]: U12.H3 (IO_L21N_T3_DQS_35); also elsewhere on the board

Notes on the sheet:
INVERTED POLARITY
INVERTED POLARITY CLK

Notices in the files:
FPGA/srcs/constrs_1/io_loc.xdc:
Copyright (C) 2019 Dejan Priversek
This program is free software: you can redistribute it and/or modify
it under the terms of the GNU General Public License as published by
the Free Software Foundation, either version 3 of the License, or
(at your option) any later version.
ScopeFun_PCB/file56770A0B.kicad_sch:
Copyright Dejan Priversek 2017
Licensed under CERN OHL v.1.2
